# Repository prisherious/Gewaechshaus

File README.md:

# Gewaechshaus

IoT Gewächshaus

## Getting Started

Diese Arbeit ist im Rahmen der 2. Projektarbeit im 7. Semester der HS Pforzheim entstanden.

### Prerequisites

Benötigte Komponenten:
```
Raspberry PI 3
Sensorik ( Siehe Parts List)
Aktorik ( Siehe Parts List)
Node-Red Installed
Raspberian auf min. 8GB SD-Karte
```

### Installing

Betriebsystem Installation:
(https://www.raspberrypi.org/documentation/installation/installing-images/)

## Run it!

## Built With
* [Node-Red] (https://nodered.org/) - Framework
* [Raspberian] (https://www.raspberrypi.org/downloads/raspbian/) - Betriebsystem

## Contributing

Please read [CONTRIBUTING.md](https://gist.github.com/PurpleBooth/b24679402957c63ec426) for details on our code of conduct, and the process for submitting pull requests to us.

## Authors

* **Maximilian Schührer** - *Initial work* - [prisherious](https://github.com/prisherious)
* **Kevin German** - *Intial work* - [Kevger](https://github.com/Kevger)

## License

This project is licensed under the MIT License - see the [LICENSE.md](LICENSE.md) file for details

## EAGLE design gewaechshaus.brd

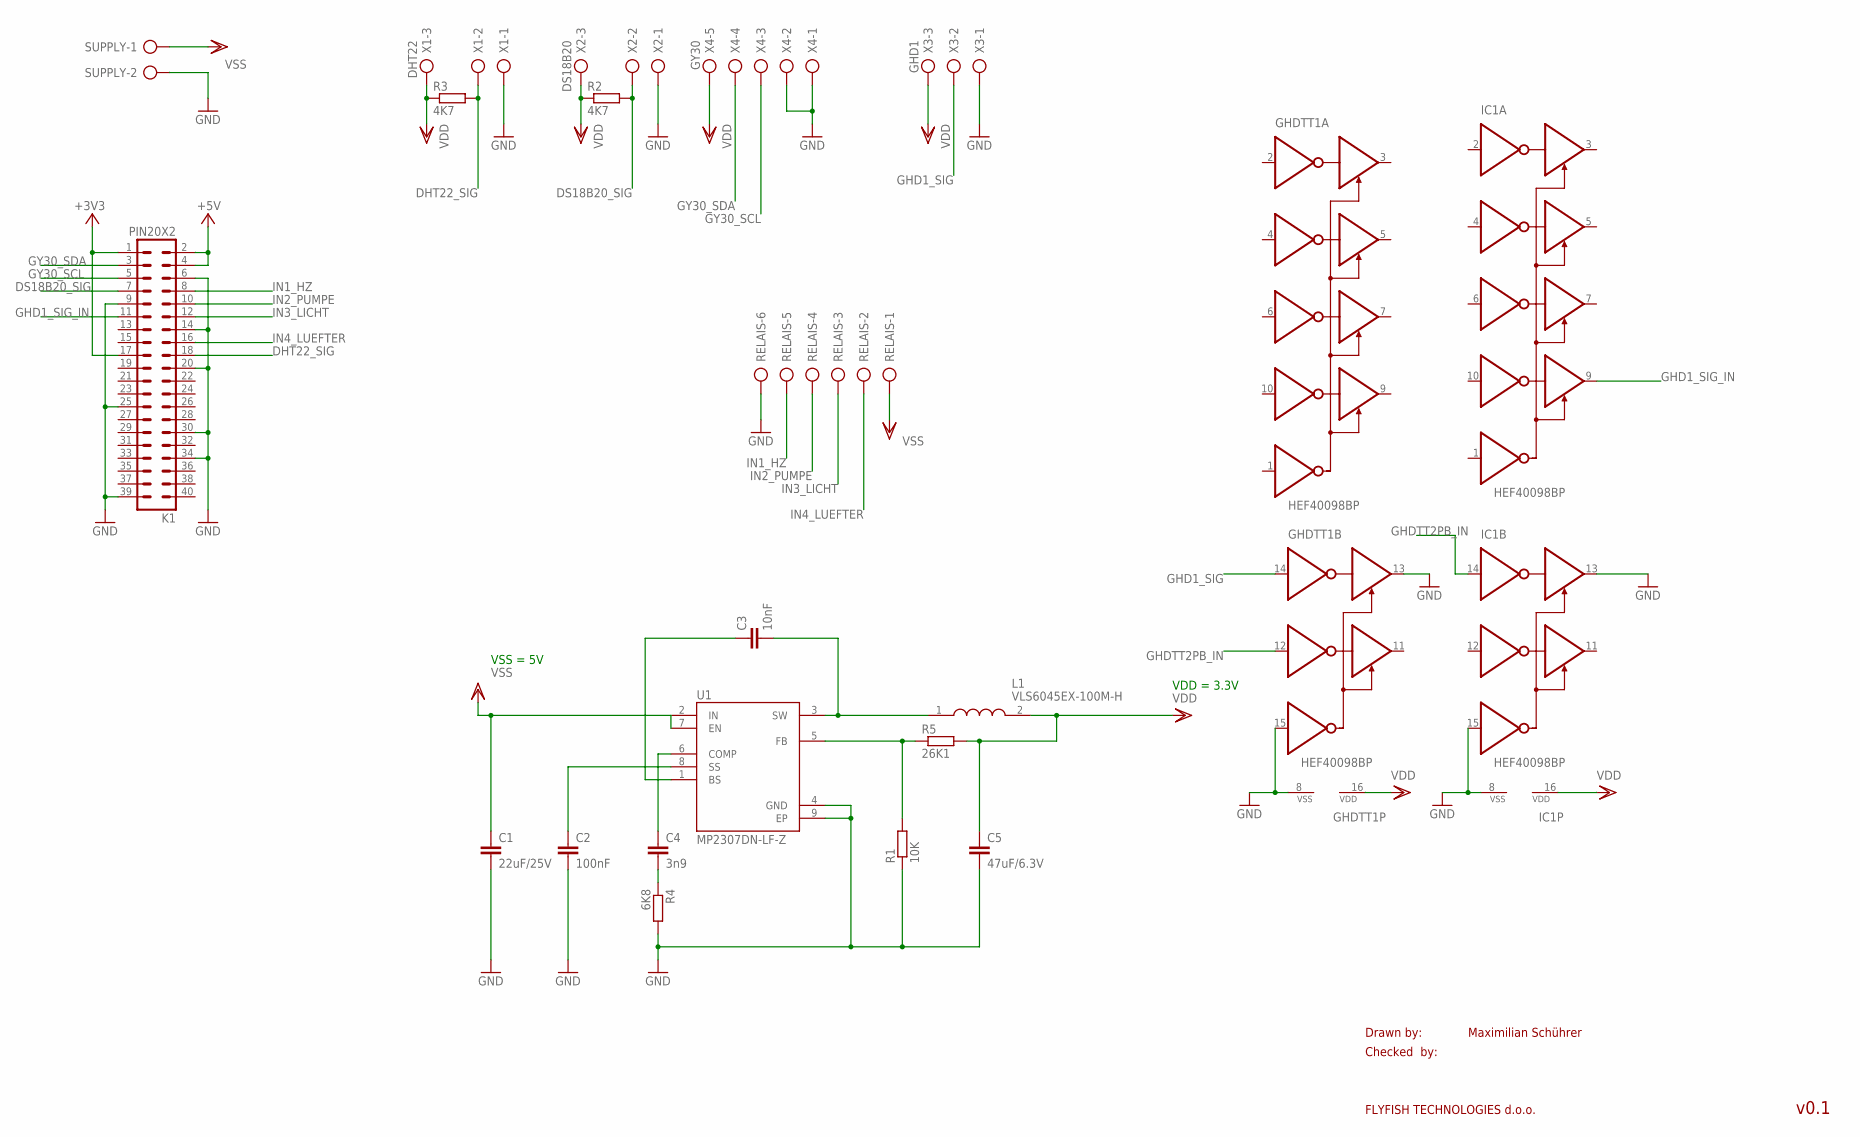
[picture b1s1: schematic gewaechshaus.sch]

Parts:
C1: 22uF/25V; C0805K
C2: 100nF; C0805K
C3: 10nF; C0805K
C4: 3n9; C0805K
C5: 47uF/6.3V; C0805K
GHDTT1: HEF40098BP; DIL16
IC1: HEF40098BP; DIL16
K1: PIN20X2; PIN_20X2
L1: VLS6045EX-100M-H; INDPM6360X450N
R1: 10K; R0805
R2, R3: 4K7; R0805
R4: 6K8; R0805
R5: 26K1; R0805
RELAIS: AK500/6
SUPPLY: AK500/2
U1: MP2307DN-LF-Z; SOIC127P600X170-9N
X1: DHT22; AK500/3
X2: DS18B20; AK500/3
X3: GHD1; AK500/3
X4: GY30; AK500/5

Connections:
+3V3: K1.1, K1.17
+5V: K1.2, K1.4
DHT22_SIG: K1.18, R3.2, X1.2
DS18B20_SIG: K1.7, R2.2, X2.2
GHD1_SIG: GHDTT1.14 (2A0), X3.2
GHD1_SIG_IN: IC1.9 (1Y3), K1.11
GHDTT2PB_IN: GHDTT1.12 (2A1), IC1.14 (2A0)
GND: C1.2, C2.2, C5.2, GHDTT1.8 (VSS), GHDTT1.13 (2Y0), GHDTT1.15 (2!OE), IC1.8 (VSS), IC1.13 (2Y0), IC1.15 (2!OE), K1.6, K1.9, K1.14, K1.20, K1.25, K1.30, K1.34, K1.39, R1.1, R4.2, RELAIS.6, SUPPLY.2, U1.4 (GND), U1.9 (EP), X1.1, X2.1, X3.1, X4.1, X4.2
GY30_SCL: K1.5, X4.3
GY30_SDA: K1.3, X4.4
IN1_HZ: K1.8, RELAIS.5
IN2_PUMPE: K1.10, RELAIS.4
IN3_LICHT: K1.12, RELAIS.3
IN4_LUEFTER: K1.16, RELAIS.2
unnamed: R1.2, R5.1, U1.5 (FB)
unnamed: C2.1, U1.8 (SS)
unnamed: C3.1, U1.1 (BS)
unnamed: C3.2, L1.1, U1.3 (SW)
unnamed: C4.1, U1.6 (COMP)
unnamed: C4.2, R4.1
VDD: C5.1, GHDTT1.16 (VDD), IC1.16 (VDD), L1.2, R2.1, R3.1, R5.2, X1.3, X2.3, X3.3, X4.5
VSS: C1.1, RELAIS.1, SUPPLY.1, U1.2 (IN), U1.7 (EN)

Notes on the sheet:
Drawn by:
Checked by:
FLYFISH TECHNOLOGIES d.o.o.
Maximilian Schührer
v0.1
VSS = 5V
VDD = 3.3V

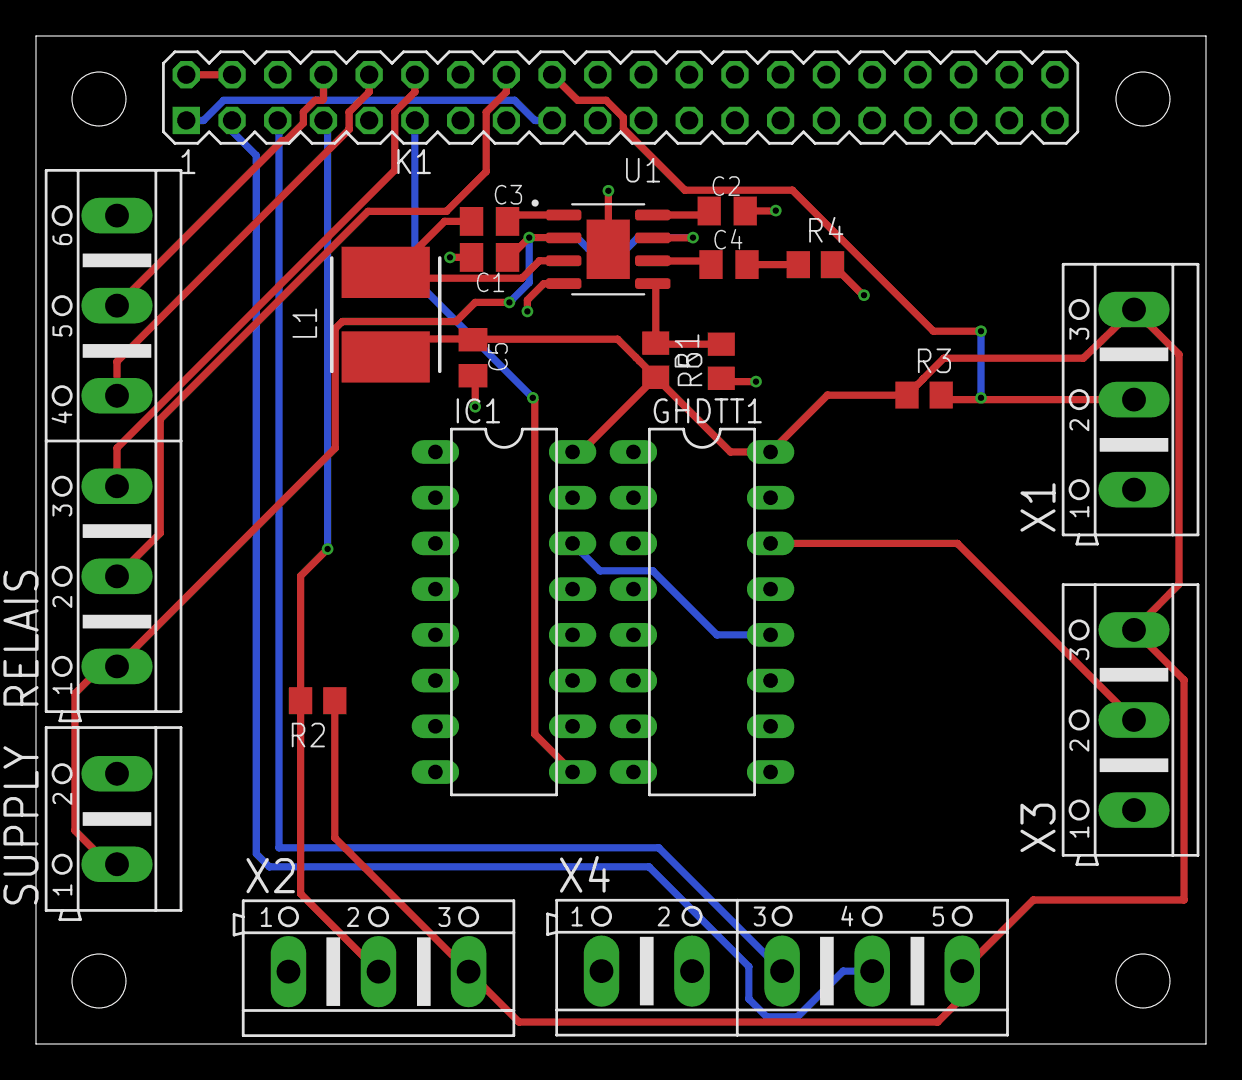
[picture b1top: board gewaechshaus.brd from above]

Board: 2 copper layers, 65.0 x 56.0 mm, 21 parts (0 on the bottom side), 22 nets.

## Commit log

2019-01-10 Schaltplan und Layout
    Eagle Projekt (*.epf)
    Schaltplan & Layout (*.pdf)
    Schaltplan & Layout (*.brd & *.sch)
    Part List (*.txt)
